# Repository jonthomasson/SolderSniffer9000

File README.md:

# SolderSniffer9000
A DIY Solder Fume Extractor for 80mm Fan with built in battery charger.

It chops, it dices, it sucks, it blows, it's the Solder Sniffer 9000! After a recent move I was in need of a more portable solder fume extractor. Previously I was using a PC PSU hooked up to a small 80mm fan to suck away solder fumes. I thought it would be neat to make a portable sucker that could be recharged with the millions of micro USB cables I have lying around. Thus the Solder Sniffer 9000 was born! This project is built around an 80mm PSU fan. I chose this type and size fan because that's what I have laying around. I figured it'd be great if I could recycle some of these fans. The main PCB attaches to one side of the fan, via the fan mounting holes. For power I'm using a protected 18650 lithium cell. I'm using the Microchip MCP73831 charge controller to charge the battery via the Micro USB port. The battery is then boosted to the 12 volts required by the fan through use of the Semtech SC4503 step up regulator.
![enter image description here](https://lh3.googleusercontent.com/lAs5yyoZNqOFHvuRhlynxwo_R--8PWqJcgd_jjI6EHcwee4sk6s7vFg0BtDzGmjtqx0Ff0_K_e3mD94I6FwvLRuabP4b_9Osu1a5uzanZ7PESfyJPfpcDF5x4c6m_dsZqu9SjoPIMi-xRggmN9L-WQcqFh_uodXpyzDGo75IKTlhL2suu6iO-AjlWmjXYyCeTcxGkubcXBfiOi8zIzAJjDwv3zhDIfAjcgcLU3EtcGCvD3KmItuLeOC7BWBvBcSpdDq4ZxQ9sqnxG9C38oQxZad5MVS4EsZ6VyIYcK1UaAa3m6MK4DGnZF30Tkba8tlnf_6ebniEX_xBxNO65Ha89tS1JD9an8yeTEGRNWsrEZngqaTCQ028t3tptYuHT6KKKAQAx6bkpCVPO1PNwZH3mZanL6cqSXucFNl5tH-hjOtgyyIlEq_f6Z3WbOMrcfS0ld4s8bgMv5UKQ9OnC6WB7HuXzkIm_ViK8hUWvy5HODw_fUdx6_mwggwSZWAzNxgVxVYTMMuFz7APe2WtVhMeX_tEjRVP0PsBDJqs0AePEmxPMksVdPCDCzqqvp4DvKC6gg9pcwwIpQPnpWDThCjEAh2slqRcaRzkDCNTtD7M=w1265-h949-no)

![enter image description here](https://lh3.googleusercontent.com/34mNDDMhwQWCEcVDpiyjnw0Z-S3oCal-eQXqZIbWolDbLpy-xn97MdiaS-pX-pZ9BGYoCawT2w7hVak32vGW6cuKDikLCVMxaWiUwZszsmvlJUHRNDMsvFF96Da90ZJn-JcUZkF9SVj919yBJZnbii5jR22rZ8GIReV5vLbZoi7sTDSb_r6bps4eJOtAaUFuuqMX7BjaK-GBKJy1KEfKuRG0O1FP2rbenojqwgaE-PiMyvIpgi1mYFfk3RmSifPi8oIMK5PgTgDyypGx5NxjRndN37IKMD1rZeX7mB-cVmUyyVplwk1igYTChXyY9iNnxlnjElJlH6oP7PINi8Au75oEEE-Xu2aRpXVn1Kz70nmb3ZZeggqwWCyQyO0x05lsAfkvH_94-cTh3nIvEgCxRewx4c7r3LsTT8riMSb6DVI0qp9nuP3o8DLDX8KPhO9j_hwKp_lncxScs3vI4ZaIXwaA9_Vc7vnMfKDeqOhQOfFd_soANJjsaJU1nOsnwcmMbxhYQOD49_to4syT8nf2r40OTvbR9O7ZXiHVC2xFQwWzOSblV03ZDUi0BUHRzks72fnwao03lcbW0WR8nHw4KWVIWLDtW7GKf2uY-3a-=w1265-h949-no)

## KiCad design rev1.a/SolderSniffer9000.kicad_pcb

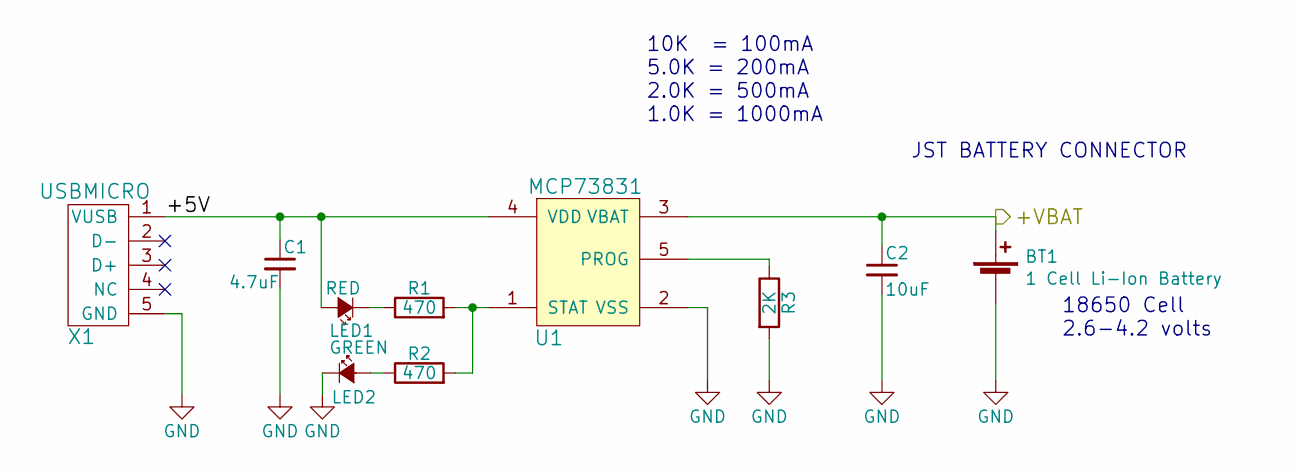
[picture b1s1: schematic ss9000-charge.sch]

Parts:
BT1: 1 Cell Li-Ion Battery; Batteries_Keystone_54
C1: 4.7uF; C_0805
C2: 10uF; C_1206
LED1: RED; LED_0805
LED2: GREEN; LED_0805
R1, R2: 470; R_0805
R3: 2K; R_0805
U1: MCP73831; Microchip_MCP73831
X1: USBMICRO; MICRO_USB_10118194

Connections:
/ss9000-charge/+5V: C1.1, LED1.2 (A), U1.4 (VDD), X1.1 (VUSB)
/ss9000-charge/+VBAT: BT1.1 (+), C2.1, U1.3 (VBAT); also elsewhere on the board
GND: BT1.2 (-), C1.2, C2.2, LED2.1 (K), R3.2, U1.2 (VSS), X1.5 (GND); also elsewhere on the board
unnamed: LED1.1 (K), R1.1
unnamed: LED2.2 (A), R2.1
unnamed: R1.2, R2.2, U1.1 (STAT)
unnamed: R3.1, U1.5 (PROG)

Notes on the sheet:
10K = 100mA 5.0K = 200mA 2.0K = 500mA 1.0K = 1000mA
JST BATTERY CONNECTOR
18650 Cell 2.6-4.2 volts

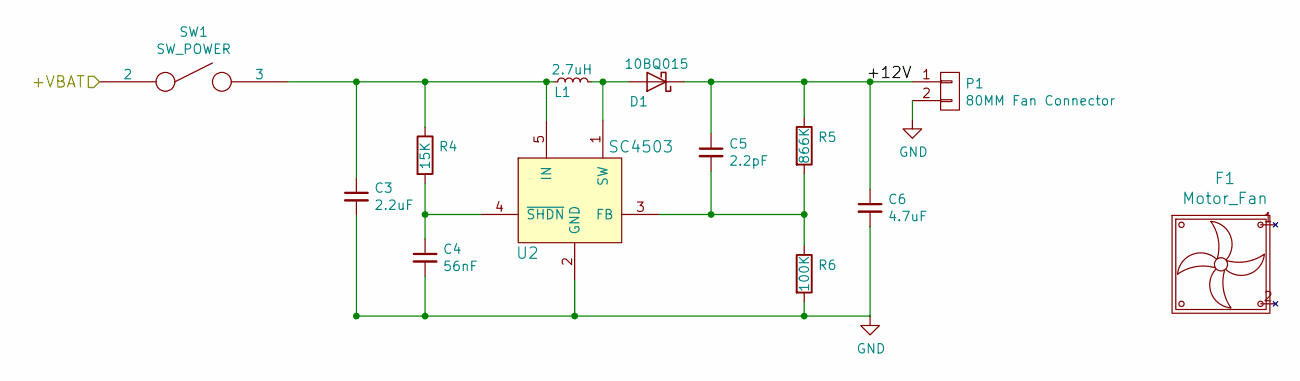
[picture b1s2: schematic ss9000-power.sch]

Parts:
C3: 2.2uF; C_0805
C4: 56nF; C_0805
C5: 2.2pF; C_0805
C6: 4.7uF; C_0805
D1: 10BQ015; do214aa
F1: Motor_Fan
L1: 2.7uH; Bourns_SRN4018_2R7M
P1: 80MM Fan Connector; Connector_OnShore_OSTTE020104
R4: 15K; R_0805
R5: 866K; R_0805
R6: 100K; R_0805
SW1: SW_POWER; Switches_C&K_SS12D07
U2: SC4503; SEMTECH-SC4503

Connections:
/ss9000-charge/+VBAT: SW1.2; also elsewhere on the board
/ss9000-power/+12V: C5.1, C6.1, D1.1 (K), P1.1, R5.1
GND: C3.2, C4.2, C6.2, P1.2, R6.2, U2.2 (GND); also elsewhere on the board
unnamed: C3.1, L1.1, R4.1, SW1.3, U2.5 (IN)
unnamed: C4.1, R4.2, U2.4 (~SHDN)
unnamed: C5.2, R5.2, R6.1, U2.3 (FB)
unnamed: D1.2 (A), L1.2, U2.1 (SW)

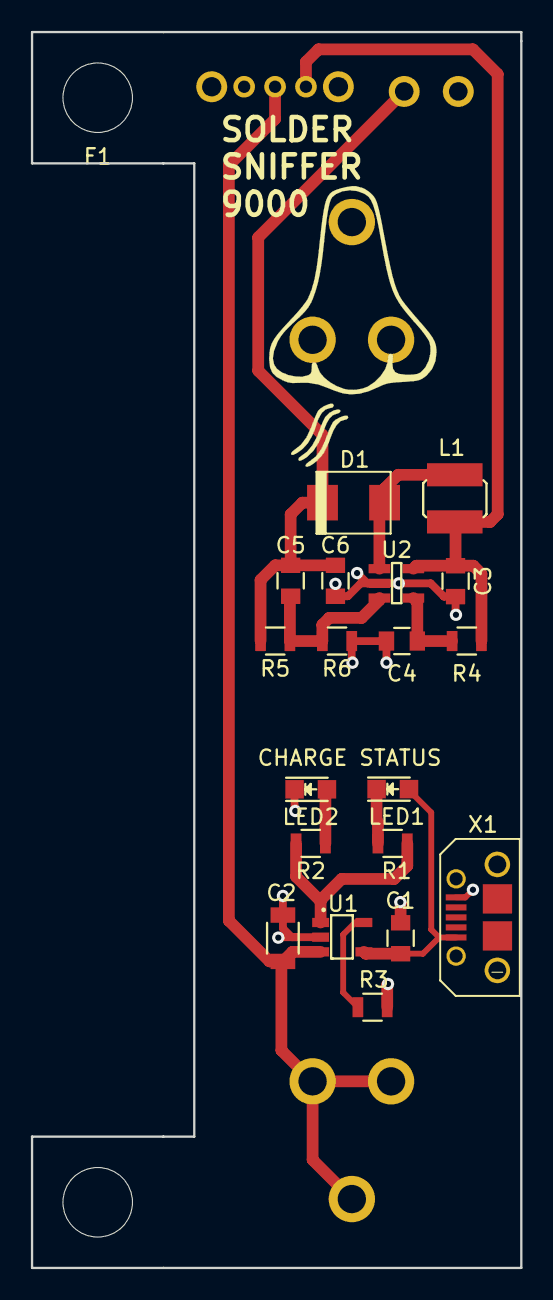
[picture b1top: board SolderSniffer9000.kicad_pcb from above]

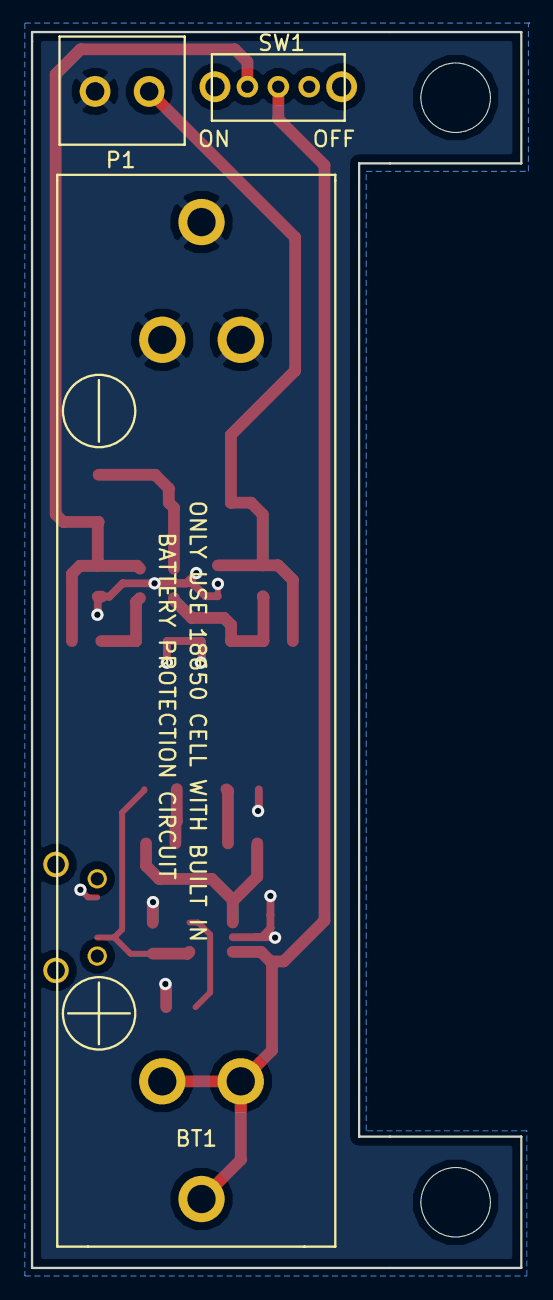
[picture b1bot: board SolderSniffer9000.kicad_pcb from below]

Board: 2 copper layers, 31.7 x 80.0 mm, 23 parts (3 on the bottom side), 12 nets.

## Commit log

2017-05-22 :boom::camel: Added .gitattributes & .gitignore files
2017-05-22 Initial Checkin
2017-06-29 cosmetic changes to silk screen and updated schematic pdf
2017-06-30 updated pcb image
2017-06-30 added bom with digikey part list
